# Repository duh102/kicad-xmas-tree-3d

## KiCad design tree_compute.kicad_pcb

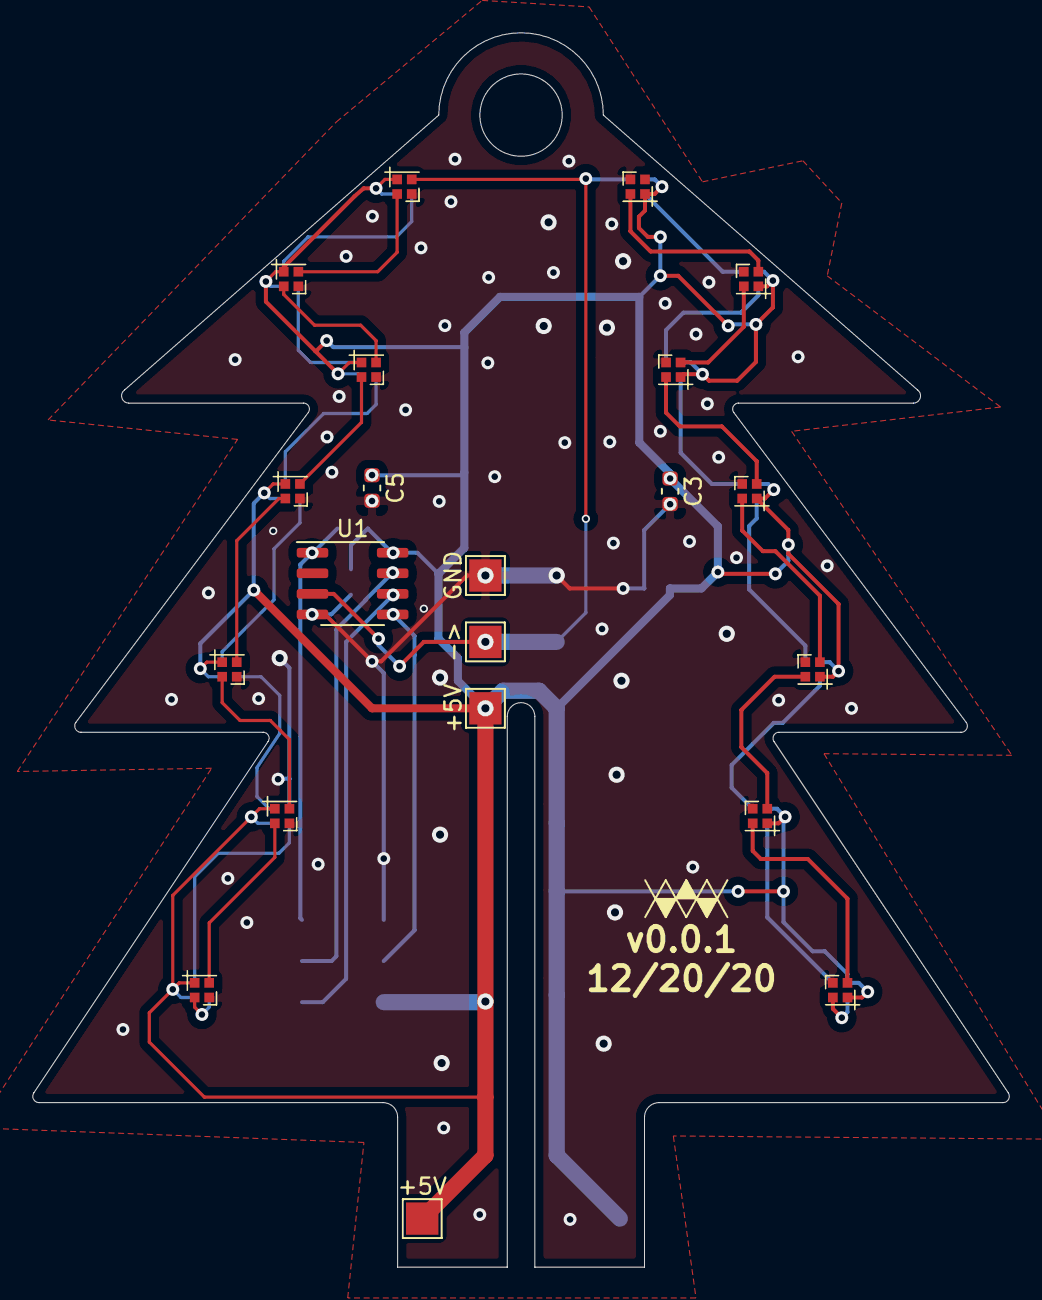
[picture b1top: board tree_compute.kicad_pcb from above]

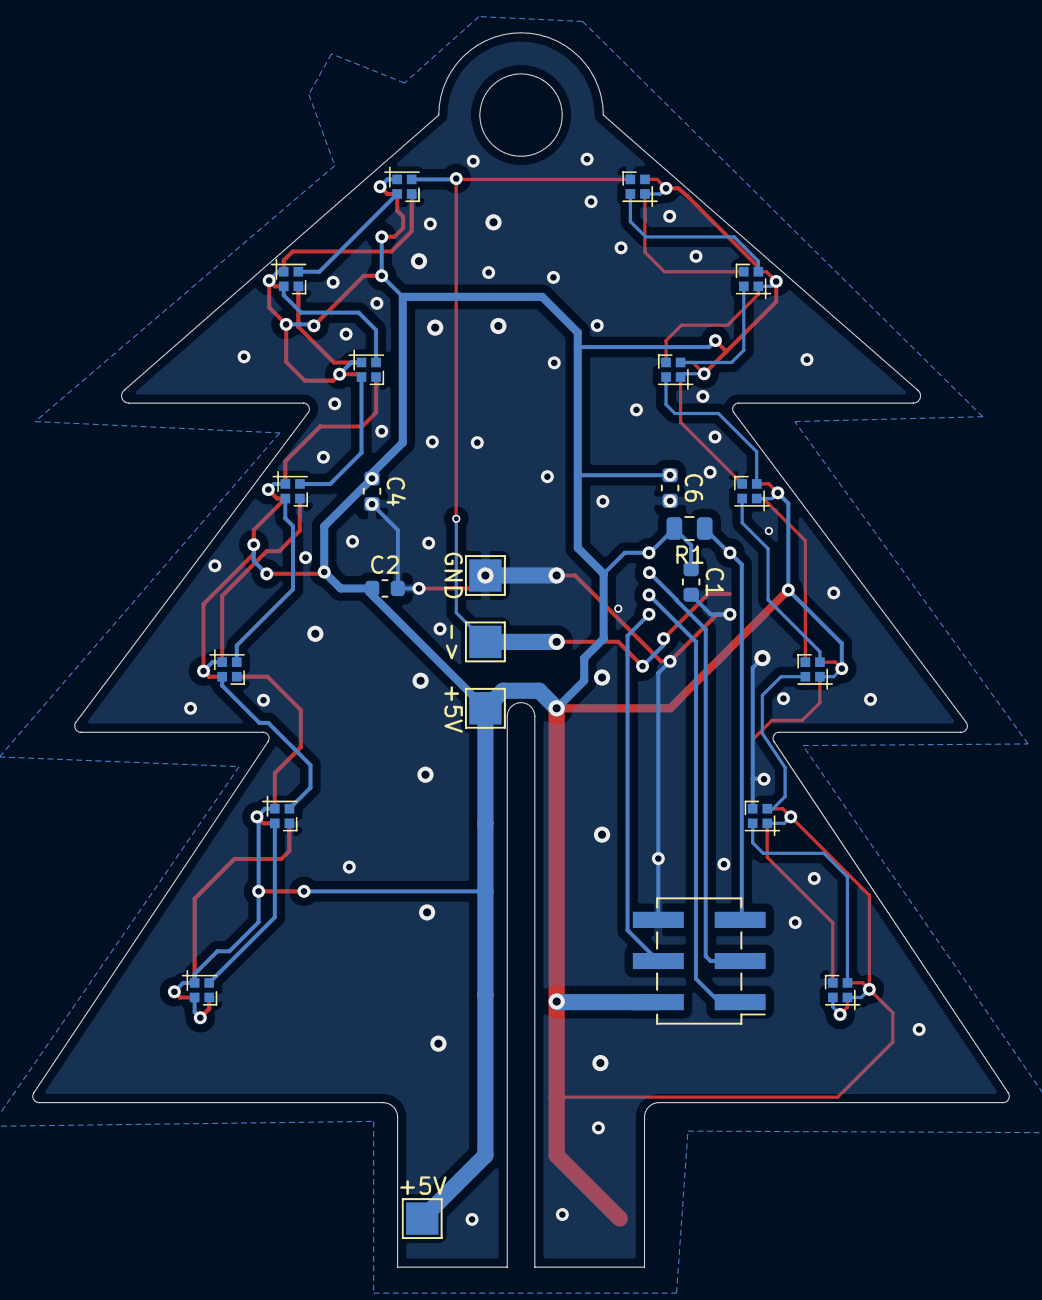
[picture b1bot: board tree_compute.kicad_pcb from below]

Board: 2 copper layers, 60.3 x 76.2 mm, 45 parts (24 on the bottom side), 33 nets.

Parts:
+5V, +5V#2, +5V#3, +5V#4: Conn_01x01; TestPoint_Pad_2.0x2.0mm
->: Conn_01x01; TestPoint_Pad_2.0x2.0mm
->#2: Conn_01x01; TestPoint_Pad_2.0x2.0mm
C1, C2: 0.1uF; C_0603_1608Metric
C3, C4, C5, C6: 1uF; C_0603_1608Metric
D1, D2, D3, D4, D5, D6, D7, D8, D9, D10, D11, D12, D13, D14, D15, D16, D17, D18, D19, D20, D21, D22, D23, D24, D25, D26, D27, D28: SK6805_1515-LED; LED_SK6805_PLCC4_1.5x1.5mm_P0.65mm
GND: Conn_01x01; TestPoint_Pad_2.0x2.0mm
GND#2: Conn_01x01; TestPoint_Pad_2.0x2.0mm
J1: AVR-ISP-6; PinHeader_2x03_P2.54mm_Vertical_SMD
R1: 10kR; R_0805_2012Metric
U1: ATtiny13A-SSU; SOIC-8_3.9x4.9mm_P1.27mm

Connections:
+5V: +5V.1, +5V#2.1, +5V#3.1, +5V#4.1, C1.1, C2.1, C3.1, C4.1, C5.1, C6.1, D1.4, D2.4, D3.4, D4.4, D5.4, D6.4, D7.4, D8.4, D9.4, D10.4, D11.4, D12.4, D13.4, D14.4, D15.4, D16.4, D17.4, D18.4, D19.4, D20.4, D21.4, D22.4, D23.4, D24.4, D25.4, D26.4, D27.4, D28.4, J1.2, R1.2, U1.8
DOUT: ->.1, ->#2.1, D1.3, D15.3, U1.3
LGND: C1.2, C2.2, C3.2, C4.2, C5.2, C6.2, D1.2, D2.2, D3.2, D4.2, D5.2, D6.2, D7.2, D8.2, D9.2, D10.2, D11.2, D12.2, D13.2, D14.2, D15.2, D16.2, D17.2, D18.2, D19.2, D20.2, D21.2, D22.2, D23.2, D24.2, D25.2, D26.2, D27.2, D28.2, GND.1, GND#2.1, J1.6, U1.4
MISO: J1.1, U1.6
MOSI: J1.4, U1.5
unnamed: D1.1, D2.3
unnamed: D2.1, D3.3
unnamed: D3.1, D4.3
unnamed: D4.1, D5.3
unnamed: D5.1, D6.3
unnamed: D6.1, D7.3
unnamed: D7.1, D8.3
unnamed: D8.1, D9.3
unnamed: D10.1, D11.3
unnamed: D9.1, D10.3
unnamed: D11.1, D12.3
unnamed: D12.1, D13.3
unnamed: D13.1, D14.3
unnamed: D15.1, D16.3
unnamed: D16.1, D17.3
unnamed: D17.1, D18.3
unnamed: D18.1, D19.3
unnamed: D19.1, D20.3
unnamed: D20.1, D21.3
unnamed: D21.1, D22.3
unnamed: D22.1, D23.3
unnamed: D23.1, D24.3
unnamed: D24.1, D25.3
unnamed: D25.1, D26.3
unnamed: D26.1, D27.3
unnamed: D27.1, D28.3
RESET: J1.5, R1.1, U1.1
SCK: J1.3, U1.7

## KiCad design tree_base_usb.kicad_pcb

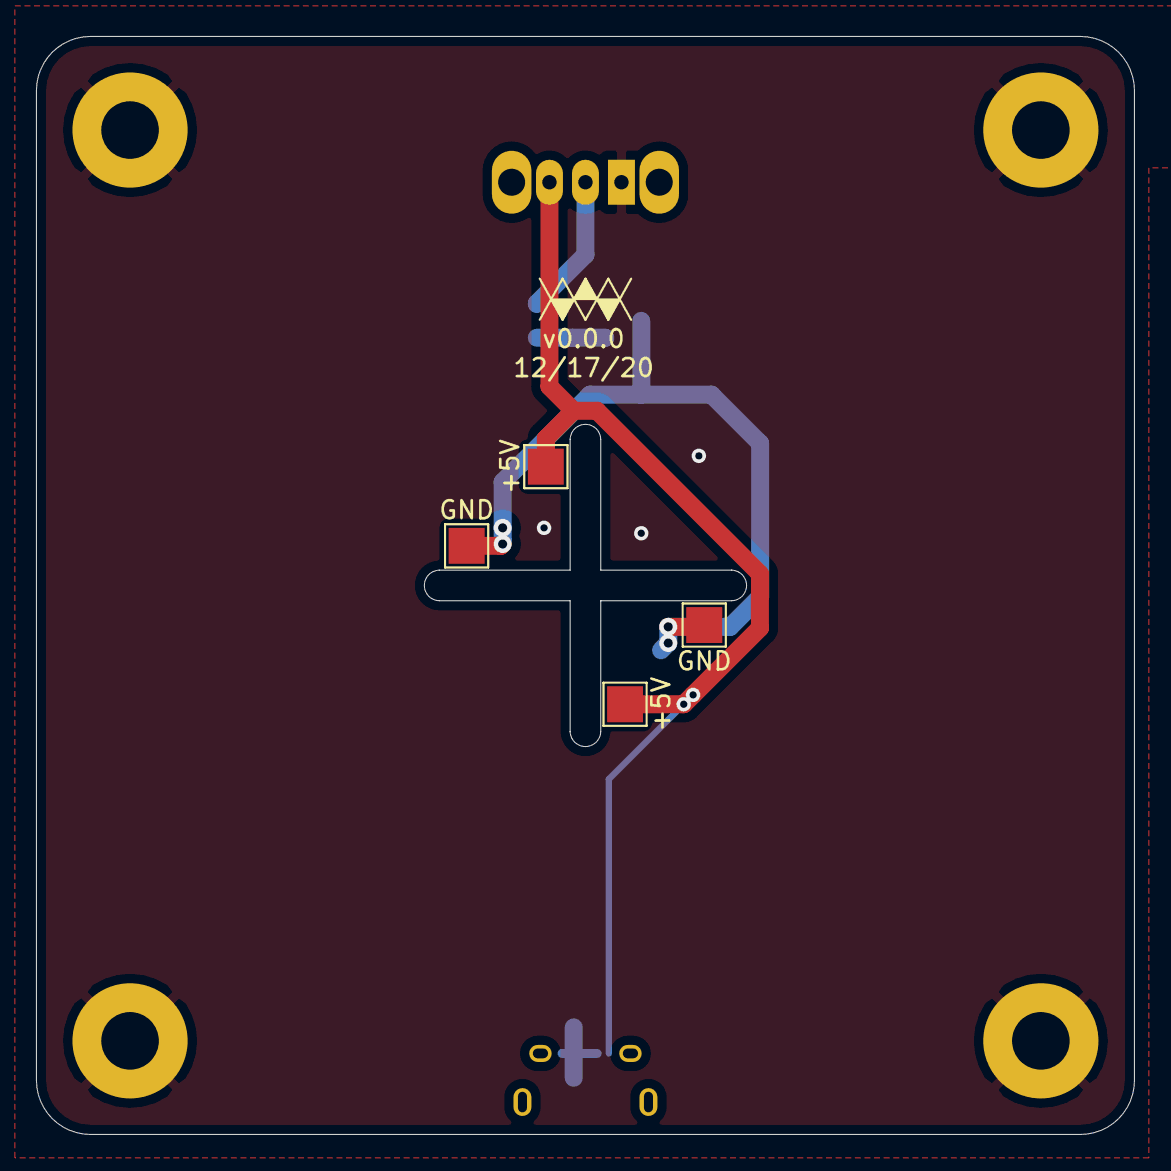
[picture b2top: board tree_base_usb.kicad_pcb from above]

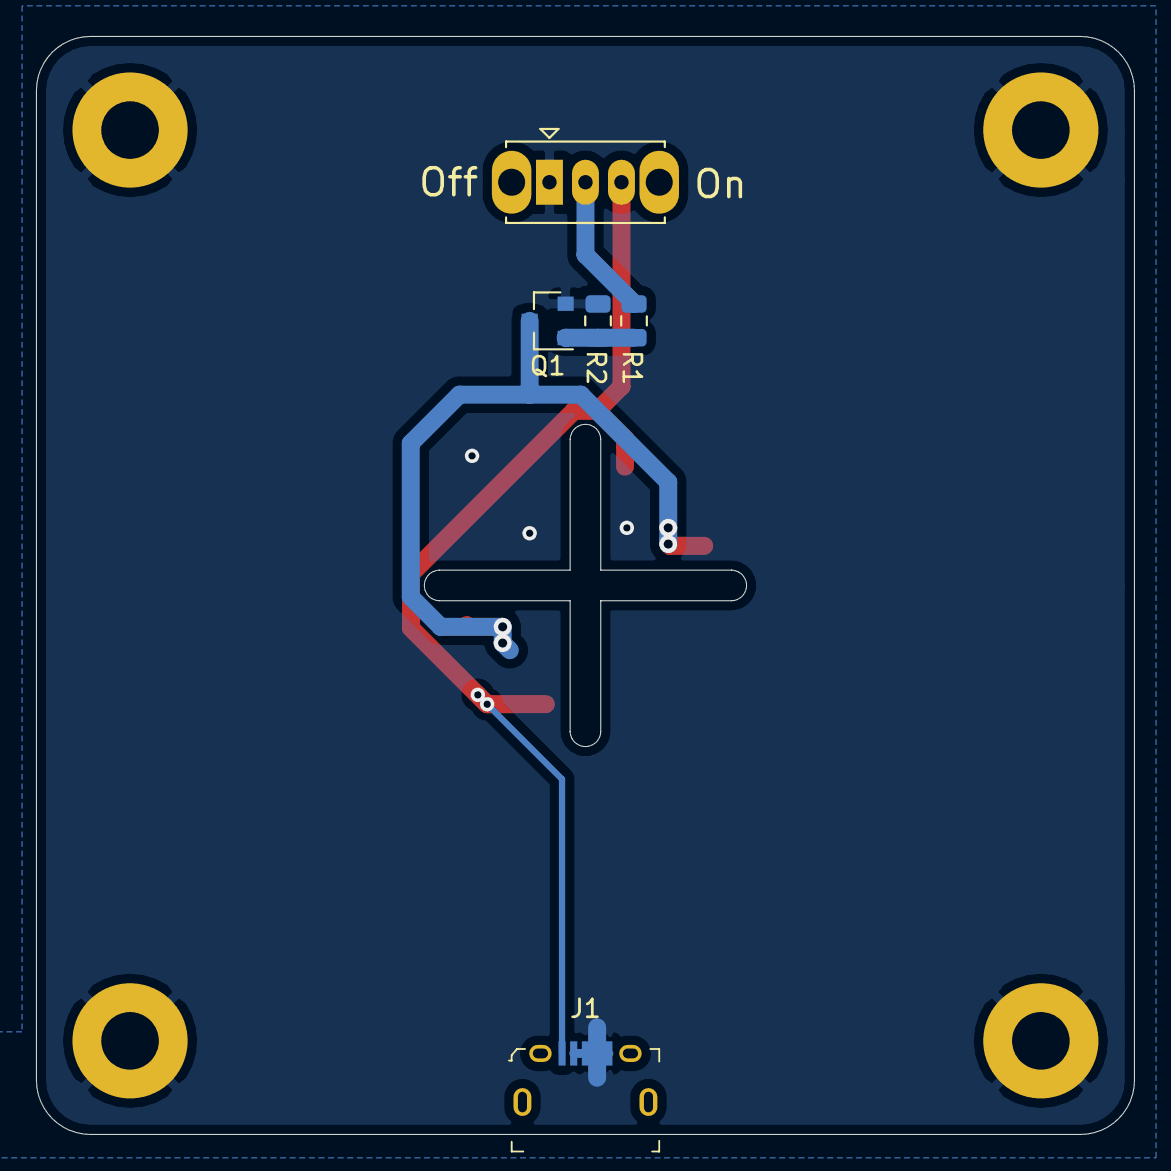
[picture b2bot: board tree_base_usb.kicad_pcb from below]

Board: 2 copper layers, 61.0 x 61.0 mm, 9 parts (5 on the bottom side), 5 nets.

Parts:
+5V, +5V#2: TP_V; TestPoint_Pad_2.0x2.0mm
GND: TP_G; TestPoint_Pad_2.0x2.0mm
GND#2: TP_G; TestPoint_Pad_2.0x2.0mm
J1: USB_B_Micro; USB_Micro_B_Female_10118194-0001LF
Q1: DMG2302U; SOT-23
R1: 1kR; R_0805_2012Metric
R2: 10kR; R_0805_2012Metric
SW1: SW_SPDT; SW_Slide_1P2T_CK_OS102011MS2Q

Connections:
+5V: +5V.1, +5V#2.1, J1.1, SW1.3
+SWV: R1.1, SW1.2
GND: J1.2, J1.3, J1.4, J1.5, Q1.2, R2.2, SW1.1
unnamed: Q1.1, R1.2, R2.1
POW_GND: GND.1, GND#2.1, Q1.3

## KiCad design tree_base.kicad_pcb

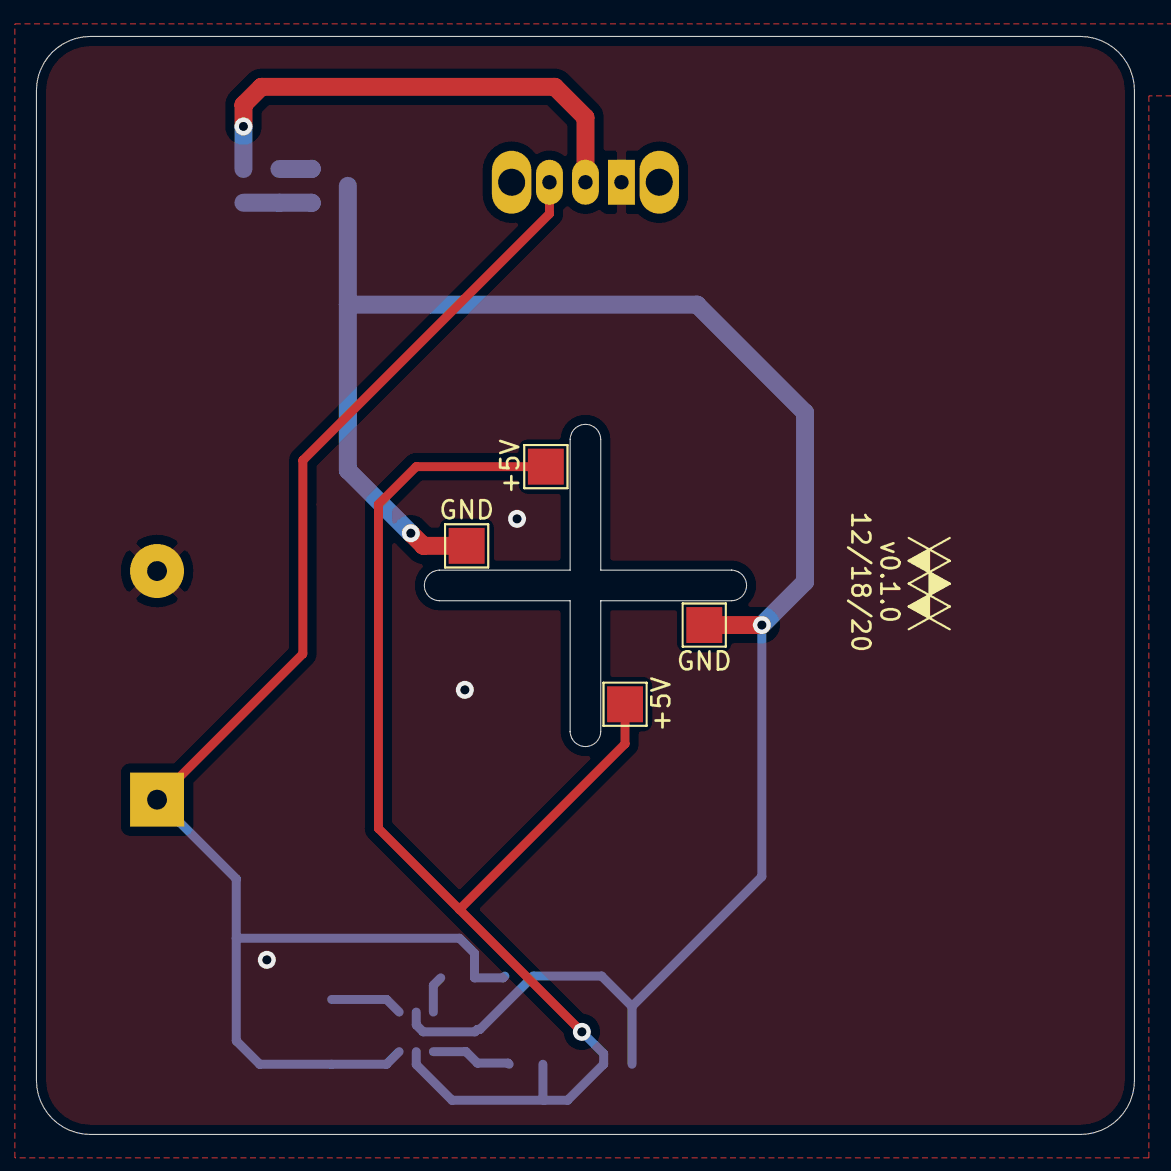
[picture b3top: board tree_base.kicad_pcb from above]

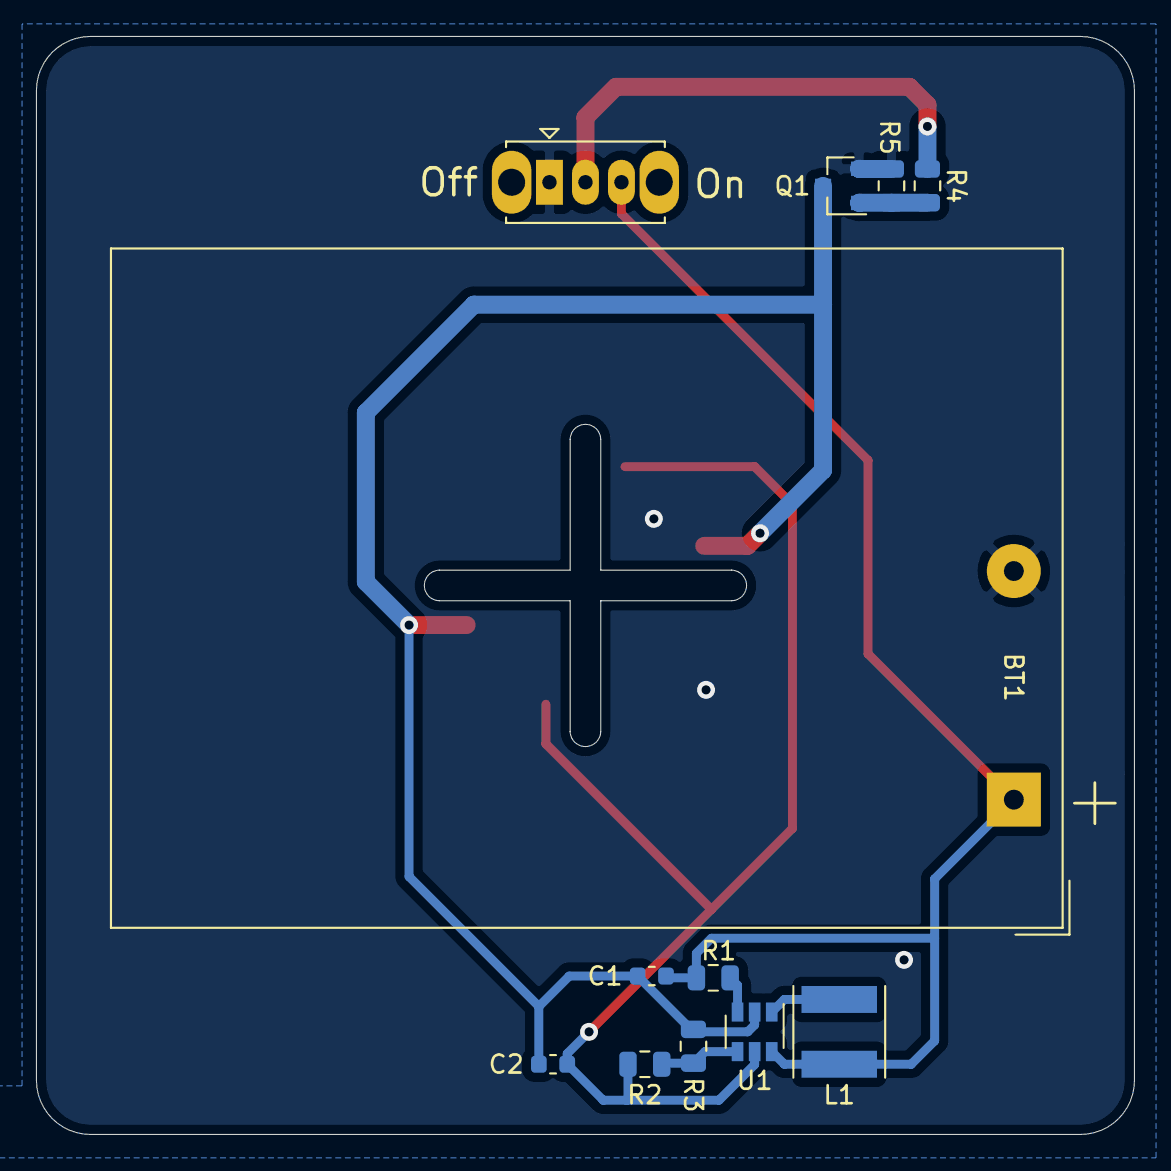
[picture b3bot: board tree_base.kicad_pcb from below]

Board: 2 copper layers, 61.0 x 61.0 mm, 16 parts (12 on the bottom side), 9 nets.

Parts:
+5V, +5V#2: TP_V; TestPoint_Pad_2.0x2.0mm
BT1: Battery; BatteryHolder_Keystone_2479_3xAAA_noscrew
C1, C2: 10uF; C_0603_1608Metric
GND: TP_G; TestPoint_Pad_2.0x2.0mm
GND#2: TP_G; TestPoint_Pad_2.0x2.0mm
L1: 10uH 1.4As; L_Taiyo-Yuden_NR-50xx
Q1: DMG2302U; SOT-23
R1, R5: 10kR; R_0805_2012Metric
R2: 976kR; R_0805_2012Metric
R3: 309kR; R_0805_2012Metric
R4: 1kR; R_0805_2012Metric
SW1: SW_SPDT; SW_Slide_1P2T_CK_OS102011MS2Q
U1: MCP1640BCH; SOT-23-6

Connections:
+1-1.5V: BT1.1, C1.1, L1.1, R1.1, SW1.3, U1.6
+5V: +5V.1, +5V#2.1, C2.1, R2.1, U1.5
+SWV: R4.1, SW1.2
GND: BT1.2, Q1.2, R5.2, SW1.1
unnamed: L1.2, U1.1
unnamed: Q1.1, R4.2, R5.1
unnamed: R1.2, U1.3
unnamed: R2.2, R3.1, U1.4
POW_GND: C1.2, C2.2, GND.1, GND#2.1, Q1.3, R3.2, U1.2

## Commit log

2020-11-25 Initial commit; base+compute complete
2020-12-09 Update with changes to use attiny13a only
2020-12-18 Add USB variant; update to use 3xAAA
2020-12-20 Move right side LEDs to back to break up pattern
